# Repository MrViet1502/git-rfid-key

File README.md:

## Used devices:
- Arduino pro mini 3v3
- MFRC522 and Cards
- Button config
- Button Power
- Buzzer
- USB UART
  
## Wiring connection diagram

- RED and Black big -> 48V
- White of Button (Pin 6)
- Graay of RESET (Pin reset)
- Blue and white big of Relay 
  ### Load code by USB UART
  - Yellow of TX
  - Green of RX
  - Black small of GND
## Link Demo:
https://youtu.be/RNAoaklGJTw

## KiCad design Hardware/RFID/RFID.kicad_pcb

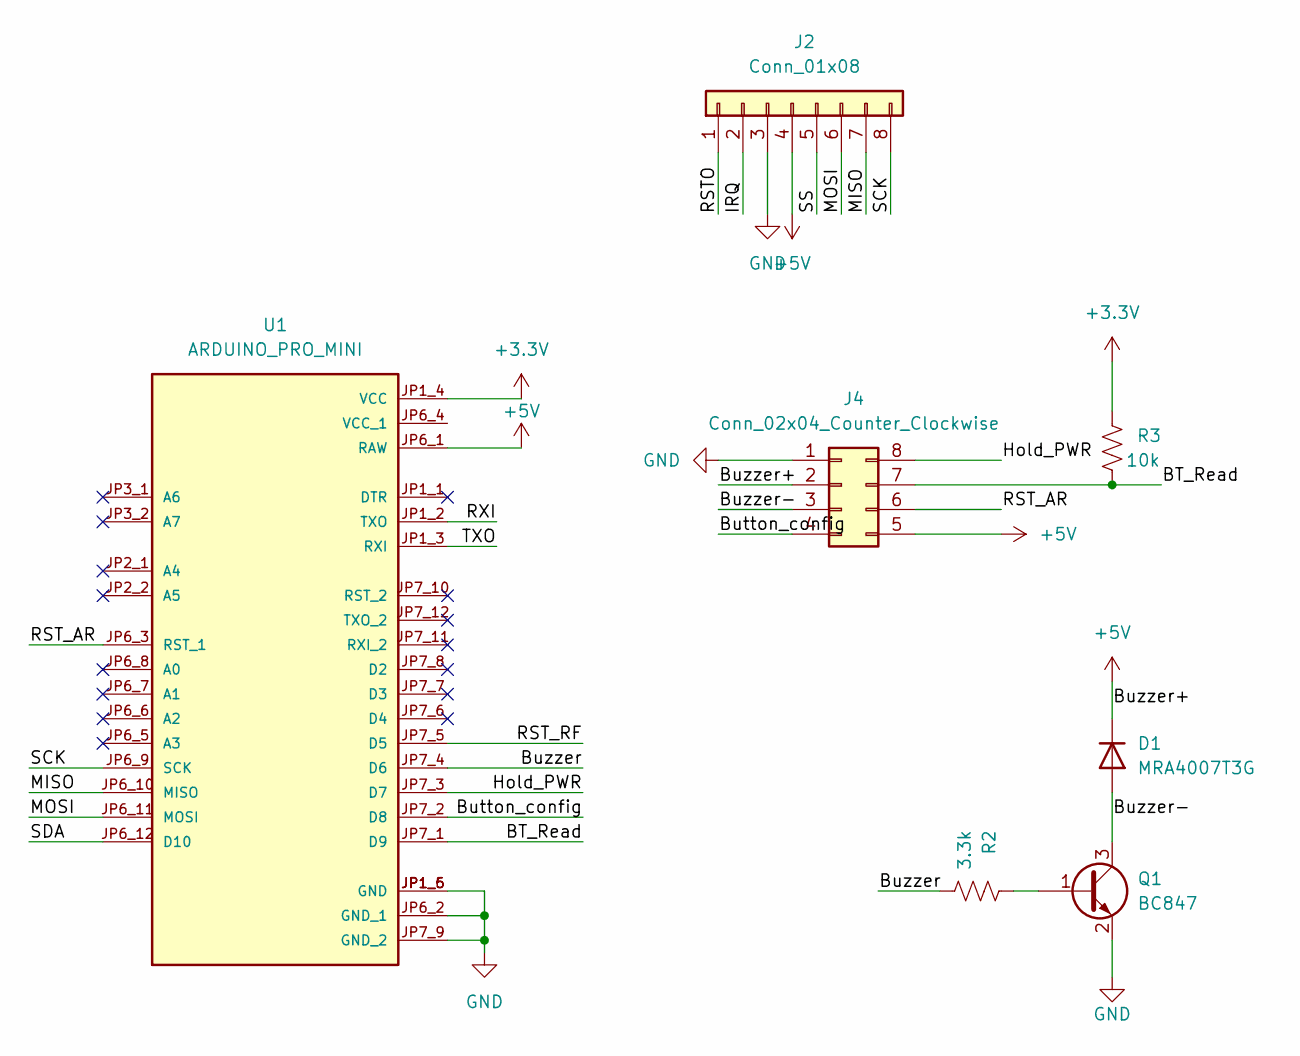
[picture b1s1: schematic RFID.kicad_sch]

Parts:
D1: MRA4007T3G; D_SMA
J2: Conn_01x08; PinHeader_1x08_P2.54mm_Vertical
J4: Conn_02x04_Counter_Clockwise; PinHeader_2x04_P2.00mm_Vertical
Q1: BC847; SOT-23
R2: 3.3k; R_0603_1608Metric
R3: 10k; R_0603_1608Metric
U1: ARDUINO_PRO_MINI; MODULE_ARDUINO_PRO_MINI; PARTREV N/A

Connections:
+3.3V: R3.1, U1.JP1_4 (VCC)
+5V: D1.1 (K), J2.4, J4.2, J4.5, U1.JP6_1 (RAW)
/BT_Read: J4.7, R3.2, U1.JP7_1 (D9)
/Button_config: J4.4, U1.JP7_2 (D8)
/Buzzer: R2.1, U1.JP7_4 (D6)
/Buzzer-: D1.2 (A), J4.3, Q1.3 (C)
/Hold_PWR: J4.8, U1.JP7_3 (D7)
/IRQ: J2.2
/MISO: J2.7, U1.JP6_10 (MISO)
/MOSI: J2.6, U1.JP6_11 (MOSI)
/RSTO: J2.1
/RST_AR: J4.6, U1.JP6_3 (RST_1)
/RST_RF: U1.JP7_5 (D5)
/RXI: U1.JP1_2 (TXO)
/SCK: J2.8, U1.JP6_9 (SCK)
/SDA: U1.JP6_12 (D10)
/SS: J2.5
/TXO: U1.JP1_3 (RXI)
GND: J2.3, J4.1, Q1.2 (E), U1.JP1_5 (GND), U1.JP1_6 (GND), U1.JP6_2 (GND_1), U1.JP7_9 (GND_2)
unnamed: Q1.1 (B), R2.2

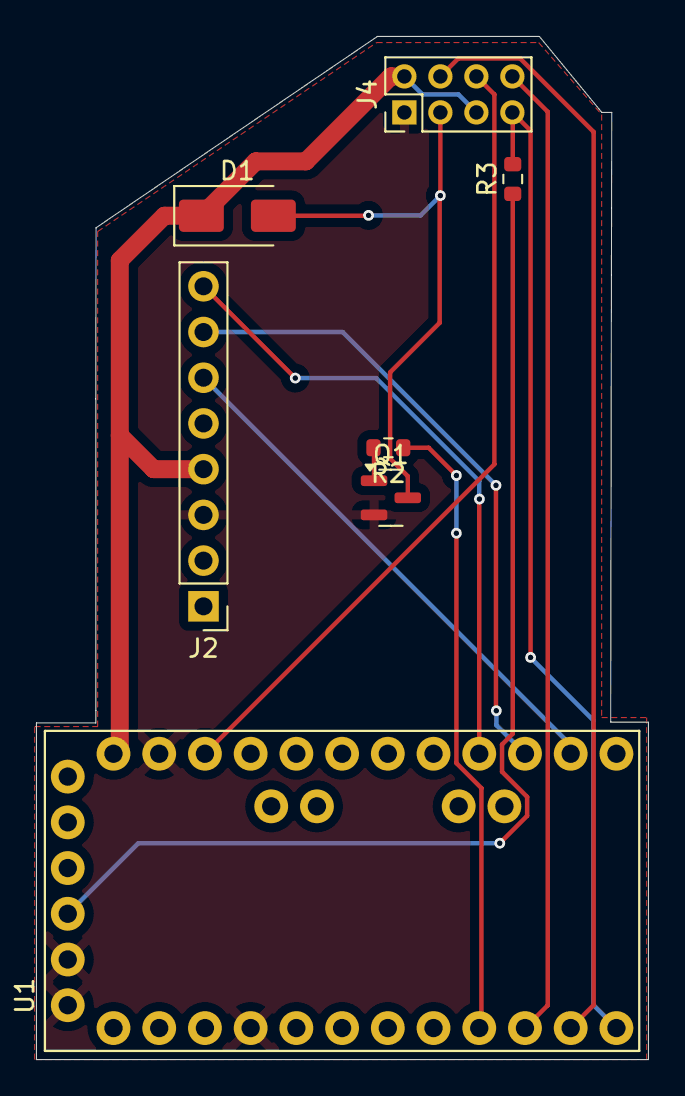
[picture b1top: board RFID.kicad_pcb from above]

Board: 2 copper layers, 34.0 x 56.8 mm, 7 parts (0 on the bottom side), 13 nets.

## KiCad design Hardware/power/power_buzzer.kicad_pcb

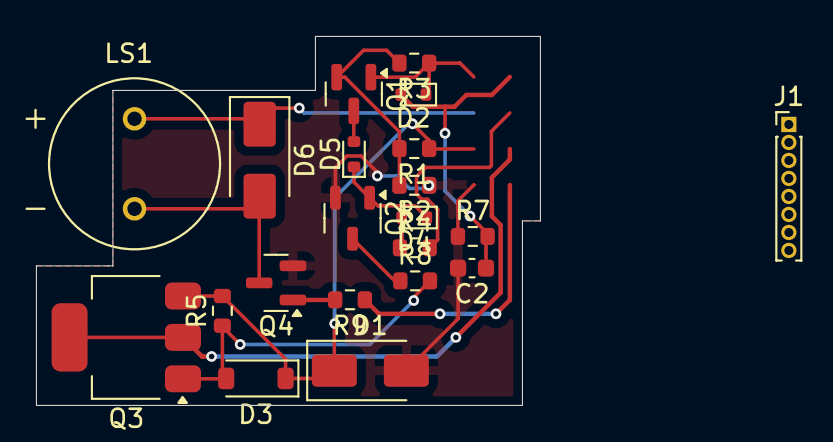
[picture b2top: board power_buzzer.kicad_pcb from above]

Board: 2 copper layers, 28.0 x 20.5 mm, 21 parts (0 on the bottom side), 15 nets.

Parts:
C2: 100n; C_0603_1608Metric
D1: SMAJ60A-E3/5A; D_SMA
D2, D4, D5: SBR0220T5-7; D_SOD-523
D3: MMSZ5246BQ-13-F; D_SOD-123
D6: MRA4007T3G; D_SMA
J1: Conn_01x08; PinHeader_1x08_P1.00mm_Vertical
LS1: AI-1027-TWT-3V-R; XDCR_AI-1027-TWT-3V-R
Q1: IRLML6402TRPBF; SOT-23
Q2: BSS123-7-F; SOT-23-3
Q3: DMP10H400SE-13; SOT-223-3_TabPin2
Q4: BC847; SOT-23
R1: 39k; R_0603_1608Metric
R2: 2.2k; R_0603_1608Metric
R3: 100k; R_0603_1608Metric
R4: 100; R_0603_1608Metric
R5: 1M; R_0603_1608Metric
R7: 10k; R_0603_1608Metric
R8: 2.2M; R_0603_1608Metric
R9: 3.3k; R_0603_1608Metric

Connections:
/+5V: D6.1 (K), LS1.P
/BT_PWR: D2.1 (K), J1.2, Q1.1 (G), R3.1
/BT_Read: C2.1, D2.2 (A), J1.1, R7.2
/Hold_PWR: J1.3, R4.2
/KEY_PWR: J1.4, J1.5, Q3.2 (D)
/V_BAT+: D1.1 (K), D3.1 (K), J1.6, Q3.3 (S), R1.1, R5.2
GND: C2.2, D1.2 (A), J1.7, J1.8, Q2.2 (S), Q4.2 (E), R2.1, R7.1
unnamed: D3.2 (A), Q3.1 (G), R5.1, R8.2
unnamed: D4.2 (A), R4.1
unnamed: D4.1 (K), D5.1 (K), Q2.1 (G)
unnamed: D5.2 (A), Q1.3 (D)
unnamed: D6.2 (A), LS1.N, Q4.3 (C)
unnamed: Q1.2 (S), R1.2, R2.2, R3.2
unnamed: Q2.3 (D), R8.1
unnamed: Q4.1 (B), R9.2

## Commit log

2024-08-02 Project RFID key using RC522 with arrduino
